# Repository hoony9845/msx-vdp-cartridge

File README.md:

# MSX V9990 / V9968 Emulator Cartridge (RP2350)

[English](#english)

MSX 실기기에서 **V9990(GFX9000)과 V9968을 가장 저렴하게 경험**해 보기 위한 프로젝트다.
실제 V9990 칩이나 FPGA 없이 RP2350 보드 하나가 MSX 버스를 받아 VDP처럼 동작하고,
화면은 HDMI(DVI 640×480@60)로 출력한다. V9990 모드에서는 I/O 포트 0x60–0x6F를 쓴다.

| MSX 실기 동작 | Geo3D 테스트 (V9968 + geo3d) |
|---|---|
|  |  |
| **Geo3D - 최적화 중** | **V9968 - 최적화 중** |
|  |  |

> **주의: 에뮬레이터다.** 실제 칩이 아니라 소프트웨어로 VDP 동작을 흉내 낸다.
> V9990은 Yamaha 매뉴얼과 openMSX 동작을, V9968은 HRA!의 RTL을 기준으로 맞췄지만,
> 실제 V9990 칩이나 V9968 카트리지(RTL)와 결과(화면, 타이밍, 커맨드 속도 등)가 다를 수 있다.
> 알려진 차이는 아래 [알려진 위험](#알려진-위험)에 정리했다.

> **면책: 사용에 따른 모든 위험은 이용자에게 있다.** 이 프로젝트의 회로도, PCB, 펌웨어,
> 소스 코드는 "있는 그대로(AS IS)" 제공되며 어떤 보증도 하지 않는다. 이를 제작하거나 사용하면서
> 생기는 MSX 본체·주변기기·모니터의 고장, 데이터 손실 등 모든 손해와 위험은 전적으로 이용자가
> 부담하며, 제작자는 어떠한 책임도 지지 않는다.

카트리지의 슬라이드 스위치(SW1, PCB rev 0.2)로 **V9968 + geo3d v2.0**(HRA!의 V9968 카트리지 호환, 포트 88h–8Fh)도 고를 수 있다.
스위치가 포트 디코더와 펌웨어 선택을 함께 바꾼다. 스위치 없는 rev 0.1 기판은 펌웨어 설정(`-DMSX_VDP_SWITCH=OFF`, USB 시리얼 `chip v9968`)으로 고른다.
자세한 내용은 [docs/v9968.md](docs/v9968.md)

- 프로토타입 보드: **Pimoroni Pico Plus 2** (RP2350B, 플래시 16MB, PSRAM 8MB)
  또는 **Waveshare Core2350B1/B2** (`-DPICO_BOARD=waveshare_core2350b`)
- 결선: [docs/hardware.md](docs/hardware.md)
- 카트리지 PCB (KiCad 8, JLCPCB 주문용 거버 포함): [hardware/](hardware/README.md)

> **실기 검증된 조합은 하나뿐이다:** Core2350B판 PCB(rev 0.3) + **Waveshare Core2350B2**(PSRAM 8MB).
> Pico Plus 2판 PCB와 Core2350B1(PSRAM 2MB)은 제작·검증하지 않았다.

## 구조

```
core/        이식 가능한 VDP 코어 (Pico SDK 의존성 없음, PC와 펌웨어가 공유)
  v9990.c        포트, 레지스터, 팔레트, 모드 해석, 타이밍 이벤트
  v9990_cmd.c    커맨드 엔진(블리터)
  v9990_render.c 스캔라인 렌더러 → RGB565
  v9990_vram.h   VRAM 물리 배치 (P1/P2/Bx 뱅크 인터리브)
  v9968*.c       V9968: 포트/레지스터, 커맨드 엔진(LRMM/LFMx 포함), 렌더러(스프라이트 모드 3)
  geo3d.c        geo3d v2.0 (참조 모델을 C로 옮김, V9968 커맨드 엔진에 명령 발행)
host/        PC용 테스트, 렌더 데모, 트레이스 재생기 (gcc)
tools/compare/  openMSX(GFX9000)와 도트 단위 비교 환경, 게임 기록 도구
firmware/    RP2350 펌웨어 (pico-sdk)
  src/bus.pio    버스 모니터 + 읽기 응답 PIO 프로그램
  src/bus.c      core1: 버스 이벤트 처리, 커맨드 엔진 실행, /INT
  src/dvi_out.c  HSTX DVI 출력, V9990 타이밍(VBlank, 라인 인터럽트)
  src/psram.c    PSRAM(VRAM) 초기화
  src/main.c     클럭(384MHz, HSTX 126MHz), 칩 선택, core0 렌더 루프
  src/vdp_select.c  칩 선택 설정 (플래시 저장, USB 시리얼 명령)
hardware/    카트리지 PCB (KiCad 프로젝트 생성 스크립트, 거버/BOM/CPL)
docs/        하드웨어 문서
```

## 동작 방식

```
MSX OUT ─► PIO monitor ─► DMA ─► 링버퍼 ─► core1 ─► v9990_write_port()
MSX IN  ─► PIO read SM ─► DMA ─► read_table[port] ─► PIO가 D0-D7 구동
                                      ▲
                     core1이 v9990_peek_port()로 항상 최신 값 유지
core0: DVI DMA IRQ ─► 렌더러가 2–3라인 앞서 v9990_render_line()
```

- 읽기는 CPU를 거치지 않고 PIO와 DMA만으로 응답하므로 Z80 I/O 사이클(약 700ns) 안에 충분히 들어온다.
- VRAM 512KB는 PSRAM에 둔다(내부 SRAM은 520KB라 부족).

## 빌드

툴체인 경로(이 머신 기준):

```sh
export PICO_SDK_PATH=~/tools/pico/pico-sdk
export PICO_TOOLCHAIN_PATH=~/tools/pico/toolchain
export PATH=~/tools/pico/cmake/bin:$PATH     # picotool 빌드에 cmake 3.17 이상 필요
```

### PC 테스트

```sh
cmake -S host -B build-host -G Ninja && ninja -C build-host
./build-host/test_v9990                           # 단위 테스트
./build-host/render_demo build-host/demo.ppm      # 640x480 출력 이미지 생성
```

### 펌웨어

```sh
cmake -S firmware -B build-fw -G Ninja && ninja -C build-fw
# BOOTSEL 상태로 연결한 뒤 build-fw/msx_v9990.uf2 복사
```

다른 RP2350B 보드:
`cmake -S firmware -B build-fw -DPICO_BOARD=<board> -DV9990_PSRAM_CS_PIN=<gpio>`

USB 시리얼 명령(진단용):

| 명령 | 내용 |
|---|---|
| `stat [reset]` | core1 루프·버스 이벤트·포트별 횟수, `/INT`·`/WAIT`, V9990 레지스터, 렌더 시간, DVI 상태(클럭 실측, 늦은 IRQ, 출력 재시작). `reset`은 최대값을 지운다 |
| `psram [sweep]` | PSRAM 쓰기/읽기 검사와 스트리밍 읽기 속도. `sweep`은 클럭 분주·RX 지연별로 검사한다 (VRAM을 지움) |
| `vram` | VRAM 64KB 블록별 CRC32 (PC 재생 결과와 비교용) |
| `out <포트> <값>` | V9990 포트에 직접 쓰기 (16진, MSX 없이 모드 시험) |
| `bench` | V9990: 현재 화면 한 줄의 렌더 시간(전체, 스프라이트 없이, VRAM 전부 SRAM일 때, 화면 꺼짐, VRAM 읽기 속도). V9968: 현재 화면 전체 줄의 평균·최대와 단계별 시간 |
| `dump` | V9968 상태(레지스터, 팔레트, VRAM)를 출력한다. 로그를 `host/v9968_dump_replay`로 PC에서 그려 볼 수 있다 (약 70초, 그동안 커맨드 엔진이 멈춤) |

`-DMSX_BOOT_TRACE=ON`으로 빌드하면 부팅 시 USB 터미널을 최대 60초 기다린 뒤 부팅 단계를 출력한다.
`stat`의 출력은 렌더 루프에서 나가므로, 주기적으로 보내면 그 프레임의 화면이 깨진다.

## 진행 상황

| 영역 | 상태 |
|---|---|
| 포트 P#0–P#7, 레지스터 쓰기 마스크, VRAM 포인터(R#2/R#5에서 갱신), 팔레트 | ✅ (PC 테스트) |
| 표시 모드 판정 (P1, P2, B1–B7, MCS 포함, 매뉴얼 8.3 표) | ✅ (PC 테스트) |
| 인터럽트 (VI, HI, CE), 상태 레지스터 | ✅ 기본 |
| P1 모드: 2레이어, 레이어별 팔레트, 앞/뒤 영역(R#27), 스크롤 | ✅ (PC 테스트) |
| P2 모드: 1024×512 이미지, 짝수/홀수 바이트 팔레트 | ✅ (PC 테스트) |
| P1/P2 스프라이트: 125개, 줄당 16개, 앞/뒤 우선순위, 팔레트 | ✅ (PC 테스트) |
| 세로 스크롤 분할(라인 중간 SCAY 쓰기), R512/R256 롤 | ✅ (PC 테스트) |
| 비트맵 렌더링 BP2/BP4/BP6/BD8/BD16 | ✅ (PC 테스트) |
| 커맨드: STOP, LMMC, LMMV, LMMM, CMMC, CMMM, LINE, PSET (비트맵 좌표계, FC/BC/WM 비트 위치 대응) | ✅ (PC 테스트) |
| 비트맵 커서 2개 (32×32, 팔레트/EOR, 커서 0 우선) | ✅ (PC 테스트, openMSX 동작 기준) |
| 펌웨어: PIO 버스, DVI 출력, PSRAM, 듀얼 코어 | ✅ 실기 확인 (Core2350B: Chase H.Q. 주행, Petscii Robots 게임 화면) |
| YJK/YUV, R#16 화면 위치 조정 | ⬜ TODO |
| 커맨드 P1/P2 좌표계 (openMSX와 같은 매핑, 실기 Ghosts'n Goblins에서 확인) | ✅ |
| 커맨드: LMCM, CMMK, BMxx, SRCH, POINT, ADVN | ⬜ TODO |
| HR 비트 (펌웨어: DVI 두 줄마다 토글) | ✅ 기본 |
| 커맨드 실행 시간, 라인 타이밍 정밀도, PAL 50Hz 타이밍 | ⬜ TODO |
| 15kHz RGB 출력 (PIO + 저항 DAC) | ⬜ 선택 사항 |
| **V9968 + geo3d v2.0** (펌웨어 설정으로 선택): 전 화면 모드, 스프라이트 모드 1–3, 전 커맨드, 인터럽트 | ✅ (PC 테스트, RTL·참조 모델·openMSX 포크와 비교) — [docs/v9968.md](docs/v9968.md) |

기준 자료: Yamaha V9990 Application Manual(1992), 매뉴얼에 없는 동작은 openMSX의 구현을 참고했다.
`tools/compare/`로 openMSX 16.0과 비교한 결과, 테스트 장면 전부가 도트 단위로 일치한다.
실제 게임에서는 다음과 같다.
- **Chase H.Q. V9990**(DiHalt Studio, 90초 플레이): 캡처 78장 중 76장이 일치한다. 나머지 2장도 그 시점의 VRAM은 openMSX와 같다(화면 스캔 타이밍 차이).
- **Another World**(Edd Biddulph, 터보 R, 4분 인트로): 113장 모두 일치한다.
- MSXdev/Mapax 작품(openMSX 60초 자동 입력, 전원 직후 화면 제외):
  - **Attack of the Petscii Robots**(P1, 스프라이트): 33장 모두 일치.
  - **MSX in a Row**(B3 BD16, LMMC, 비트맵 커서): 21장 일치, 11장은 0.1% 미만(커서 아래 끝 1줄, 미확인).
  - **Dreams Puzzle**(B3 BD16, LINE), **Mr. Balloon remake**(B7 1024 BP4): VRAM이 26/30 시점에서 같고,
    나머지는 직전 프레임에 시작된 커맨드 영역뿐이다(openMSX는 커맨드에 시간이 걸림). B7 화면은 openMSX
    캡처가 640픽셀로 줄어 도트 비교를 할 수 없다.
- **Ghosts'n Goblins**(ASM Team, V9990 데모, Konami SCC 2MB, B1 BP6/BP4 + P1 스프라이트, P1에서 LMMV/LMMM):
  직접 플레이한 기록 66장 모두 일치. P1 커맨드 좌표계가 없을 때는 악마 스프라이트가 깨졌다.
펌웨어의 렌더러는 스캔보다 2–3줄 앞서 그리므로, 화면 중간의 레지스터 변경은 몇 줄 일찍 적용된다(TODO).
새 프레임은 첫 줄 4줄 전에 시작한다(라인 카운터 리셋): 그 전에 VI 핸들러가 쓴 스크롤이 첫 줄부터 적용된다.

코드의 `VERIFY` 주석은 V9990 Application Manual이나 openMSX와 아직 대조하지 않은 부분이다
(표시 모드 표, 비트 순서, NX/NY=0의 의미 등).

## 다음 단계

1. 다른 GFX9000 소프트웨어(P1/P2, 스프라이트, 커맨드 엔진)로 실기 호환성 테스트
2. PAL(R#7 bit 3) 게임: VI를 50Hz로 낼지 결정 (HDMI 출력은 60Hz 고정)
3. 커맨드 엔진 속도: 게임 진행 중 PSRAM 경합으로 렌더 시간이 늘어난다 (B1 평균 34us/63us)

## 알려진 위험

- **읽기마다 `/WAIT`**: 읽기 SM이 모든 읽기에서 `/WAIT`를 걸고, core1이 앞선 접근을 모두 처리한 뒤에 응답한다
  (쓰기 직후의 상태 읽기, 같은 포트 연속 읽기도 순서대로 맞는다). 그만큼 읽기 사이클이 길어진다. core1이 20us 안에
  응답하지 못하면 `stat`의 ordered-read timeouts가 늘어난다.
- **렌더 시간**: VRAM0(물리 0x00000-0x3FFFF)은 SRAM, VRAM1은 PSRAM이다. 비트맵 한 줄은 XIP 스트리밍 DMA로
  읽는다(126MHz). 한계에 가까운 모드: B3 512×424 BD8 줄당 약 29us(한계 31.7us), P1(Petscii Robots)
  평균 60us(한계 63us). BD16 512×424는 아직 측정하지 않았다.
- **P1/P2 이름 표 캐시**: 이름 표 한 줄은 타일 행(8줄)마다 한 번 읽는다. 프레임 중간에 바뀐 이름은 그 타일 행의
  나머지 줄에서 다음 프레임에 보일 수 있다.
- **PSRAM 126MHz**: Core2350B 한 장에서 RX 지연 2–5가 정상(3 사용). 온도 여유는 미확인.
- **384MHz 오버클럭 + 1.30V**: clk_sys는 pll_usb(384MHz), HSTX는 pll_sys(252MHz)/2. HSTX 분주기는 정수
  분주만 되고 듀티 보정이 없어서, clk_sys/3(378MHz)에서는 모니터 화면이 대부분 검게 나왔다. Core2350B 한 장에서
  확인했고 개체별·온도별 여유는 미확인.
- **V9968 2줄 앞서 렌더**: 스프라이트 모드 3이 많은 화면(LUMEN FORGE)은 줄당 최대 약 90us라 바로 앞 줄에서
  그리면(31.7us) 늦는다. 대신 줄 인터럽트로 바꾼 레지스터가 실제 카트리지보다 2줄 늦게 보인다.
- **V9968 LRMM 속도**: core1의 LRMM이 실제 칩(픽셀당 약 12클럭)보다 수 배 느려서, LRMM으로 화면 전체를
  그리는 데모(SUPER CAT 약 11fps)는 실제보다 느리게 움직인다. 결과는 HRA의 vdp_command.v와 같다.

## 참고

- Yamaha V9990 E-VDP-III Application Manual
- openMSX `src/video/v9990/` (동작만 참고, 코드는 가져오지 않음)
- pico-examples `hstx/dvi_out_hstx_encoder`

## 라이선스

- 소프트웨어(`core/`, `firmware/`, `host/`, `tools/`): MIT (`LICENSE`)
- 하드웨어(`hardware/`): CERN-OHL-P v2 (`hardware/LICENSE`)
- 예외: V9968 코어(`core/v9968*.c`, `core/v9968.h`)는 HRA!의 V9968 RTL을 따라 만들었기 때문에
  그 RTL의 조건을 따른다(저작권 표시 유지, 허락 없는 판매·상업적 사용 금지).
  이 코어가 들어간 펌웨어 바이너리(`.uf2`)를 배포할 때도 같은 표시를 함께 넣어야 한다.
- 외부 코드와 참고 자료의 표시: `THIRD_PARTY_NOTICES.md`
- 모든 라이선스는 보증 없이(AS IS) 제공되며, 사용에 따른 위험과 책임은 이용자에게 있다(위의 면책 참고).

---

# English

This project is the **cheapest way to try the V9990 (GFX9000) and the V9968 on a real MSX**.
There is no real V9990 chip or FPGA: a single RP2350 board listens to the MSX bus and behaves like the VDP,
and the picture goes out over HDMI (DVI 640×480@60). In V9990 mode it uses I/O ports 0x60–0x6F.

| On a real MSX | Geo3D test (V9968 + geo3d) |
|---|---|
|  |  |
| **Geo3D - optimisation in progress** | **V9968 - optimisation in progress** |
|  |  |

> **Note: this is an emulator.** The VDP is imitated in software, not built as a chip.
> The V9990 follows the Yamaha manual and openMSX's behaviour, the V9968 follows HRA!'s RTL,
> but results (picture, timing, command speed, ...) can differ from a real V9990 chip or the V9968
> cartridge (RTL). Known differences are listed under [Known risks](#known-risks).

> **Disclaimer: you use this project entirely at your own risk.** The schematics, PCB, firmware and
> source code are provided "AS IS", without any warranty. All damage and risk from building or using
> them, including failure of the MSX, peripherals or monitor and loss of data, are borne entirely by
> the user; the author accepts no liability whatsoever.

The cartridge's slide switch (SW1, PCB rev 0.2) also selects **V9968 + geo3d v2.0** (compatible with HRA!'s
V9968 cartridge, ports 88h–8Fh). The switch changes both the port decoder and the firmware's choice.
On the rev 0.1 board without the switch, choose in the firmware (`-DMSX_VDP_SWITCH=OFF`, USB serial `chip v9968`).
Details: [docs/v9968.md](docs/v9968.md) (Korean)

- Prototype boards: **Pimoroni Pico Plus 2** (RP2350B, 16MB flash, 8MB PSRAM)
  or **Waveshare Core2350B1/B2** (`-DPICO_BOARD=waveshare_core2350b`)
- Wiring: [docs/hardware.md](docs/hardware.md) (Korean)
- Cartridge PCB (KiCad 8, with Gerbers for JLCPCB): [hardware/](hardware/README.md) (Korean)

> **Only one combination has been verified on hardware:** the Core2350B PCB (rev 0.3) + **Waveshare Core2350B2** (8MB PSRAM).
> The Pico Plus 2 PCB and the Core2350B1 (2MB PSRAM) have not been built or tested.

## Layout

```
core/        portable VDP core (no Pico SDK dependencies, shared by the PC and the firmware)
  v9990.c        ports, registers, palette, mode decoding, timing events
  v9990_cmd.c    command engine (blitter)
  v9990_render.c scanline renderer -> RGB565
  v9990_vram.h   physical VRAM layout (P1/P2/Bx bank interleave)
  v9968*.c       V9968: ports/registers, command engine (incl. LRMM/LFMx), renderer (sprite mode 3)
  geo3d.c        geo3d v2.0 (reference model ported to C, issues commands to the V9968 engine)
host/        PC tests, render demo, trace replayers (gcc)
tools/compare/  dot-exact comparison against openMSX (GFX9000), game recording tools
firmware/    RP2350 firmware (pico-sdk)
  src/bus.pio    bus monitor + read response PIO programs
  src/bus.c      core1: bus events, command engine, /INT
  src/dvi_out.c  HSTX DVI output, V9990 timing (VBlank, line interrupts)
  src/psram.c    PSRAM (VRAM) setup
  src/main.c     clocks (384MHz, HSTX 126MHz), chip selection, core0 render loop
  src/vdp_select.c  chip selection setting (stored in flash, USB serial command)
hardware/    cartridge PCB (KiCad project generator scripts, Gerbers/BOM/CPL)
docs/        hardware documents
```

## How it works

```
MSX OUT ─► PIO monitor ─► DMA ─► ring buffer ─► core1 ─► v9990_write_port()
MSX IN  ─► PIO read SM ─► DMA ─► read_table[port] ─► PIO drives D0-D7
                                      ▲
                     core1 keeps it current with v9990_peek_port()
core0: DVI DMA IRQ ─► renderer runs v9990_render_line() 2–3 lines ahead
```

- Reads are answered by PIO and DMA alone, without the CPU, well inside a Z80 I/O cycle (about 700ns).
- The 512KB of VRAM lives in PSRAM (the 520KB of internal SRAM is not enough).

## Build

Toolchain paths (on the development machine):

```sh
export PICO_SDK_PATH=~/tools/pico/pico-sdk
export PICO_TOOLCHAIN_PATH=~/tools/pico/toolchain
export PATH=~/tools/pico/cmake/bin:$PATH     # picotool needs cmake 3.17 or later
```

### PC tests

```sh
cmake -S host -B build-host -G Ninja && ninja -C build-host
./build-host/test_v9990                           # unit tests
./build-host/render_demo build-host/demo.ppm      # 640x480 output image
```

### Firmware

```sh
cmake -S firmware -B build-fw -G Ninja && ninja -C build-fw
# connect in BOOTSEL mode and copy build-fw/msx_v9990.uf2
```

Other RP2350B boards:
`cmake -S firmware -B build-fw -DPICO_BOARD=<board> -DV9990_PSRAM_CS_PIN=<gpio>`

USB serial commands (diagnostics):

| Command | What it does |
|---|---|
| `stat [reset]` | core1 loop, bus events, counts per port, `/INT` and `/WAIT`, V9990 registers, render times, DVI state (measured clocks, late IRQs, output restarts). `reset` clears the maxima |
| `psram [sweep]` | PSRAM write/read check and streaming read speed. `sweep` checks every clock divider and RX delay (clears VRAM) |
| `vram` | CRC32 of each 64KB VRAM block (to compare with a PC replay) |
| `out <port> <value>` | write a V9990 port directly (hex; tries modes without an MSX) |
| `bench` | V9990: render time of one line of the current picture (full, without sprites, with all VRAM in SRAM, display off, VRAM read speed). V9968: average and maximum over all lines of the current picture, per stage |
| `dump` | prints the V9968 state (registers, palette, VRAM); `host/v9968_dump_replay` draws the log on the PC (about 70 s, the command engine stops meanwhile) |

Built with `-DMSX_BOOT_TRACE=ON`, the firmware waits up to 60 s for a USB terminal at boot and prints the boot steps.
`stat` prints from the render loop, so sending it periodically breaks the picture of that frame.

## Status

| Area | Status |
|---|---|
| Ports P#0–P#7, register write masks, VRAM pointers (updated on R#2/R#5), palette | ✅ (PC tests) |
| Display mode decoding (P1, P2, B1–B7, incl. MCS, manual table 8.3) | ✅ (PC tests) |
| Interrupts (VI, HI, CE), status registers | ✅ basic |
| P1: two layers, palette per layer, front/back areas (R#27), scrolling | ✅ (PC tests) |
| P2: 1024×512 image, even/odd byte palettes | ✅ (PC tests) |
| P1/P2 sprites: 125, 16 per line, front/back priority, palettes | ✅ (PC tests) |
| Vertical scroll splits (SCAY written mid-line), R512/R256 roll | ✅ (PC tests) |
| Bitmap rendering BP2/BP4/BP6/BD8/BD16 | ✅ (PC tests) |
| Commands: STOP, LMMC, LMMV, LMMM, CMMC, CMMM, LINE, PSET (bitmap coordinates, FC/BC/WM bit positions) | ✅ (PC tests) |
| Two bitmap cursors (32×32, palette/EOR, cursor 0 first) | ✅ (PC tests, after openMSX's behaviour) |
| Firmware: PIO bus, DVI output, PSRAM, dual core | ✅ on hardware (Core2350B: Chase H.Q. racing, Petscii Robots in game) |
| YJK/YUV, R#16 display adjust | ⬜ TODO |
| Command P1/P2 coordinate systems (same mapping as openMSX, checked with Ghosts'n Goblins on hardware) | ✅ |
| Commands: LMCM, CMMK, BMxx, SRCH, POINT, ADVN | ⬜ TODO |
| HR bit (firmware: toggles every two DVI lines) | ✅ basic |
| Command timing, line timing accuracy, PAL 50Hz timing | ⬜ TODO |
| 15kHz RGB output (PIO + resistor DAC) | ⬜ optional |
| **V9968 + geo3d v2.0** (chosen by the firmware setting): all screen modes, sprite modes 1–3, all commands, interrupts | ✅ (PC tests, compared with the RTL, the reference model and the openMSX fork) — [docs/v9968.md](docs/v9968.md) |

References: Yamaha V9990 Application Manual (1992); where the manual is silent, openMSX's implementation.
Compared with openMSX 16.0 through `tools/compare/`, every test scene matches dot for dot.
In real games:
- **Chase H.Q. V9990** (DiHalt Studio, 90 s of play): 76 of 78 captures match. For the other 2 the VRAM at that moment equals openMSX's (a difference in scan timing).
- **Another World** (Edd Biddulph, turbo R, 4-minute intro): all 113 match.
- MSXdev/Mapax titles (60 s of automatic input in openMSX, power-on screens excluded):
  - **Attack of the Petscii Robots** (P1, sprites): all 33 match.
  - **MSX in a Row** (B3 BD16, LMMC, bitmap cursor): 21 match, 11 differ by under 0.1% (one line at the bottom of the cursor, not investigated).
  - **Dreams Puzzle** (B3 BD16, LINE), **Mr. Balloon remake** (B7 1024 BP4): VRAM equal at 26 of 30 points;
    the rest is only the area of a command started in the previous frame (openMSX gives commands time).
    The B7 picture cannot be compared dot by dot because openMSX scales its capture to 640 pixels.
- **Ghosts'n Goblins** (ASM Team, V9990 demo, Konami SCC 2MB, B1 BP6/BP4 + P1 sprites, LMMV/LMMM in P1):
  all 66 shots of a recorded play match. Without the P1 command coordinates the demon sprite was garbled.

The firmware renderer draws 2–3 lines ahead of the scan, so register changes mid-picture take effect a few lines early (TODO).
A new frame starts 4 lines before its first line (line counter reset), so scroll values written by the VI handler apply from the first line.

`VERIFY` comments in the code mark what has not yet been checked against the V9990 Application Manual or openMSX
(the display mode table, bit orders, the meaning of NX/NY = 0, ...).

## Next steps

1. Compatibility tests on hardware with other GFX9000 software (P1/P2, sprites, command engine)
2. PAL games (R#7 bit 3): decide whether VI runs at 50Hz (the HDMI output is fixed at 60Hz)
3. Command engine speed: PSRAM contention during play lengthens render times (B1 average 34us of 63us)

## Known risks

- **`/WAIT` on every read**: the read SM asserts `/WAIT` on every read and answers after core1 has applied every
  earlier access (a status read right after a write, or back-to-back reads of one port, come out in order). Read
  cycles get longer by that much. If core1 does not answer within 20us, `stat` counts an ordered-read timeout.
- **Render time**: VRAM0 (physical 0x00000-0x3FFFF) is in SRAM, VRAM1 in PSRAM. A bitmap line is read with XIP
  streaming DMA (126MHz). Modes near the limit: B3 512×424 BD8 about 29us a line (limit 31.7us), P1 (Petscii Robots)
  60us average (limit 63us). BD16 512×424 not measured yet.
- **P1/P2 name table cache**: a name table row is read once per tile row (8 lines). A name changed mid-frame may
  show on the remaining lines of that tile row only in the next frame.
- **PSRAM at 126MHz**: RX delays 2–5 work on one Core2350B (3 is used). Temperature margin unknown.
- **384MHz overclock at 1.30V**: clk_sys from pll_usb (384MHz), HSTX from pll_sys (252MHz)/2. The HSTX divider
  only divides by integers and has no duty-cycle correction, so at clk_sys/3 (378MHz) the monitor showed mostly black.
  Checked on one Core2350B; margins across boards and temperatures unknown.
- **V9968 renders two lines ahead**: pictures with much sprite mode 3 (LUMEN FORGE) take up to about 90us a line,
  too late when drawn just before the line (31.7us). In exchange, registers changed by line interrupts show two lines
  later than on the real cartridge.
- **V9968 LRMM speed**: LRMM on core1 is several times slower than the real chip (about 12 clocks per pixel), so demos
  that draw the whole picture with LRMM (SUPER CAT about 11 fps) move slower than on the real thing. The results
  equal HRA's vdp_command.v.

## References

- Yamaha V9990 E-VDP-III Application Manual
- openMSX `src/video/v9990/` (behaviour only, no code taken)
- pico-examples `hstx/dvi_out_hstx_encoder`

## License

- Software (`core/`, `firmware/`, `host/`, `tools/`): MIT (`LICENSE`)
- Hardware (`hardware/`): CERN-OHL-P v2 (`hardware/LICENSE`)
- Exception: the V9968 core (`core/v9968*.c`, `core/v9968.h`) follows HRA!'s V9968 RTL and therefore keeps
  that RTL's conditions (keep the copyright notice; no sale or commercial use without permission).
  Firmware binaries (`.uf2`) containing this core must carry the same notice when distributed.
- Notices for third-party code and references: `THIRD_PARTY_NOTICES.md`
- All licences come without warranty (AS IS); the risk and responsibility of use lie with the user (see the disclaimer above).

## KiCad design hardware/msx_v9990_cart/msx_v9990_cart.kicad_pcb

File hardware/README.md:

# MSX V9990 카트리지 PCB (KiCad 8)

RP2350 모듈을 얹는 MSX 카트리지 기판. 회로 설명은 [../docs/hardware.md](../docs/hardware.md) 참고.
같은 생성 스크립트로 두 가지 버전을 만든다(외형, 엣지 커넥터, 구멍 H1/H2, 버스 회로는 동일).

| 버전 | 모듈 | KiCad 프로젝트 | 제조 파일 | 빌드 |
|---|---|---|---|---|
| Pico Plus 2 | Pimoroni Pico Plus 2 (2×20 핀헤더) | `msx_v9990_cart/` | `fab/` | `./build.sh` |
| Core2350B | Waveshare Core2350B **B1(2MB) 또는 B2(8MB) PSRAM판** (2×8 핀헤더 4개) | `msx_v9990_cart_core2350b/` | `fab_core2350b/` | `MSX_VARIANT=core2350b ./build.sh` |

> **검증 상태:** 실기에서 확인한 것은 **Core2350B판 rev 0.3 + Waveshare Core2350B2(PSRAM 8MB)** 뿐이다.
> Pico Plus 2판과 Core2350B1(PSRAM 2MB) 조합은 제작·검증하지 않았다.

### Core2350B 버전 메모

- PSRAM이 모듈 뒷면에 있으므로 **반드시 핀헤더로 띄워서** 장착한다. 모듈 아래에는 배선과 비아가 지나간다.
- USB, BOOTSEL, RESET은 모듈의 **FFC 커넥터 + Waveshare USB 어댑터**를 쓴다(카트리지에는 없음).
  FFC 커넥터는 모듈 왼쪽 위 모서리 쪽에 오며, 케이블은 모듈 위로 지나간다.
- 전원: MSX +5V → D1(쇼트키) → 모듈 VBUS. USB 어댑터 연결 시 USB 전원이 MSX 쪽으로 역류하지 않는다.
- GPIO 할당과 PSRAM CS(GP47)는 Pico Plus 2판과 같다. 펌웨어는 `cmake -DPICO_BOARD=waveshare_core2350b`로 빌드.
- 모듈 핀 배치는 Waveshare 회로도(Core2350B.pdf)의 P1–P4 헤더와 제품 사진의 실크 표기를 대조해 정했다.
  **주문 전에 구멍 확인용 PDF(`fab_core2350b/*_hole_check*.pdf`) 위에 모듈 실물을 올려 확인할 것.**
- 패드 번호: 1–16 = P1, 17–32 = P2, 33–48 = P3, 49–64 = P4.

- **rev 0.2**: VDP 선택 슬라이드 스위치 SW1(C&K JS202011AQN, DPDT 직각형)을 기판 위쪽 가장자리, HDMI 커넥터 오른쪽에 추가했다(레버가 위쪽 가장자리 밖으로 약 1.2mm 나옴).
  - SW1이 디코더 비교값(V9990: 60h–6Fh, V9968: 88h–8Fh)과 GP22를 바꾼다.
  - 보조 부품으로 R10/R11(10k)을 추가했다.
  - GP22는 /WR 대신 SW1을 읽는다. U2는 /WR을 받지만 출력은 비워 둔다.
  - SW1은 스루홀 부품이라 손으로 납땜한다. 카트리지 케이스를 쓰면 레버 자리를 파 줘야 한다.
- **rev 0.3**: 외곽선을 Overrich 카트리지 케이스(Konami형)에 맞췄다.
  - 기준은 MSXLegend의 KC MSX FLASH V3 거버(Overrich 케이스용, github.com/msxlegend/KC-MSX-FLASH)이고, 엣지 핑거 끝선에 맞춰 옮겨 왔다.
  - rev 0.2 대비 차이:
    - 위로 1.96mm, 왼쪽 0.4mm, 오른쪽 0.9mm 넓어졌다.
    - 엣지 탭이 2.07mm 길어졌다(11.89mm).
    - 왼쪽 아래 노치가 2.4mm 높아졌다.
    - 케이스 기둥 구멍 H1/H2가 Ø5.0에서 Ø4.36으로 바뀌고 약 0.7mm 위로 올라갔다.
  - 핑거 위치와 치수(1.5 × 8 mm, 2.54mm 피치)는 그대로다.
  - 엣지 탭이 길어진 만큼 버스 IC U1–U3을 2mm 위로 올렸다(핑거에서 IC로 들어가는 배선 자리).
  - HDMI 커넥터(J2)와 SW1은 위쪽 가장자리를 따라 같이 올라갔고, SW1은 오른쪽 모서리에서 8mm 안쪽(x 116.5 → 108.5)으로 옮겼다. 케이스 위쪽에 HDMI 구멍과 SW1 레버 자리는 직접 파야 한다.
  - 기판 폭이 100mm를 넘어서(101.09mm) JLCPCB 최저가(100 × 100 mm 이하) 구간에서 벗어난다.
- 2층, 1.6mm, 101.09 × 64.77 mm (엣지 탭 64.79 × 11.89 mm)
- 엣지 커넥터 치수는 실제 슬롯에 맞는 것으로 검증된 costarc의 MSX-Protoboard 카트리지를 따르고, 외곽선과 기둥 구멍은 Overrich 케이스용 KC MSX FLASH V3를 따름
- 홀수 핀은 뒷면(B.Cu), 짝수 핀은 앞면(F.Cu)에 있고, 앞면에서 볼 때 1·2번 핀이 오른쪽 끝

## 파일

```
hardware/
  build.sh                 전체 재생성: 회로도 → PCB → 자동 배선 → GND 면 → ERC/DRC → 제조 파일
  gen/design.py            ★ 넷리스트의 원본 (부품, 핀-넷 연결). 회로를 바꿀 때는 여기만 수정
  gen/gen_schematic.py     회로도(.kicad_sch)와 프로젝트 심볼 라이브러리 생성
  gen/gen_pcb.py           배치, 외곽선, 실크, 금지 영역, HDMI 팬아웃
  gen/route.py             Freerouting 자동 배선 (여러 전략을 시도해 미배선 0인 결과 사용)
  gen/finish_pcb.py        GND 팬아웃, 앞뒷면 GND 면, 스티칭 비아
  gen/export_fab.py        거버, 드릴, BOM, CPL, 회로도 PDF
  gen/export_hole_check.py 구멍 위치 확인용 1:1 인쇄 PDF (fab/*_hole_check.pdf)
  msx_v9990_cart/          KiCad 프로젝트 (KiCad에서 열어 보거나 수정 가능)
  fab/                     ★ JLCPCB 주문용 출력물
  reports/                 ERC / DRC 보고서
```

KiCad에서 직접 수정해도 되지만, `build.sh`를 다시 실행하면 덮어쓰니 주의.
생성기를 고치는 쪽을 권장한다.

```sh
cd hardware && ./build.sh      # 2~5분 (자동 배선 포함)
```

필요한 것: KiCad 8 (`kicad-cli`, pcbnew 파이썬 모듈), `~/tools/freerouting/freerouting-2.4.1.jar`, Java 25 (`~/tools/jre25`).

## 검증 결과 (현재 버전)

| 항목 | 결과 |
|---|---|
| ERC | 0 errors, 0 warnings |
| DRC (회로도 일치 검사 포함) | 0 violations, 미연결 0, 풋프린트 오류 0 |
| 넷리스트 대조 | design.py와 회로도 넷 일치 (DRC schematic parity) |

## JLCPCB 주문

업로드: `fab/msx_v9990_cart_gerbers_jlcpcb.zip`

| 항목 | 값 |
|---|---|
| Layers | 2 |
| Dimensions | 101.09 × 64.77 mm (자동 인식) |
| PCB Thickness | **1.6 mm** |
| Surface Finish | ENIG 권장 (HASL도 가능) |
| **Gold Fingers** | **Yes**, **45° finger chamfer(베벨) 선택** |
| Min via hole | 0.3 mm |
| Min track/spacing | 0.15 mm (GND 면의 가장 좁은 부분 0.14 mm, JLC 최소 0.127 mm 이내) |

SMT 조립까지 맡길 경우:
- `fab/msx_v9990_cart_bom_jlcpcb.csv`, `fab/msx_v9990_cart_cpl_jlcpcb.csv` 업로드
- BOM의 `LCSC Part #` 칸은 비워 두었다. JLC 부품 검색에서 MPN으로 찾아 채울 것
- M1(Pico Plus 2)은 손으로 핀헤더 장착, SW1(스루홀 슬라이드 스위치)도 손납땜
- J2(HDMI)는 스루홀 실드 핀이 있어 CPL에서 빠져 있다. 손납땜하거나 JLC 부품이 있으면 추가할 것
- JLC 미리보기에서 SOIC 부품의 회전 방향(1번 핀 위치)을 반드시 확인할 것

## 조립 순서

1. SMD 부품: U1–U5 (SOIC), R1–R9, C1–C7, D1 (방향: 캐소드 띠가 Pico 쪽)
2. J2 HDMI 커넥터
3. M1: **2×20 핀헤더로 장착** (소켓 또는 직접 납땜). 모듈 아래로 신호선과 비아가 지나가므로 모듈을 기판에 바로 붙이지 말 것
4. 펌웨어 기록 (USB-C, BOOTSEL) 후 MSX에 삽입. **실크의 "LABEL SIDE / PINS 2-50" 면이 카트리지 라벨 방향**

## 주문 전에 직접 확인할 것

자동 검사(ERC/DRC)로는 잡을 수 없는 항목들이다.

1. **엣지 커넥터 방향**: 이 기판은 msx.org 위키와 두 오픈소스 카트리지 설계의 공통 규칙을 따랐다(짝수 핀이 라벨면).
   가지고 있는 상용 카트리지에서 1번 핀(/CS1) 쪽이 어느 면 어느 끝인지 한 번 대조할 것.
2. **HDMI 커넥터 품번**: 풋프린트는 Amphenol 10029449-x01xLF 기준이다. 다른 제품을 사면 핀 간격과 실드 위치가 다를 수 있다.
3. **Pico Plus 2 핀배치**: Raspberry Pi Pico와 같은 40핀 배치(GND 3·8·13·18·23·28·33·38번, VSYS 39번, 3V3 36번)라고 가정했다. Pimoroni 핀아웃 문서로 확인할 것.
4. **슬롯 높이 여유**: 핀헤더로 올린 Pico 높이는 약 10mm다. 사용할 MSX의 슬롯 덮개와 간섭하지 않는지 확인할 것.
5. **/BUSDIR**: 오픈 드레인(74LVC07)으로 구동하며 본체에 풀업이 있다고 가정했다.

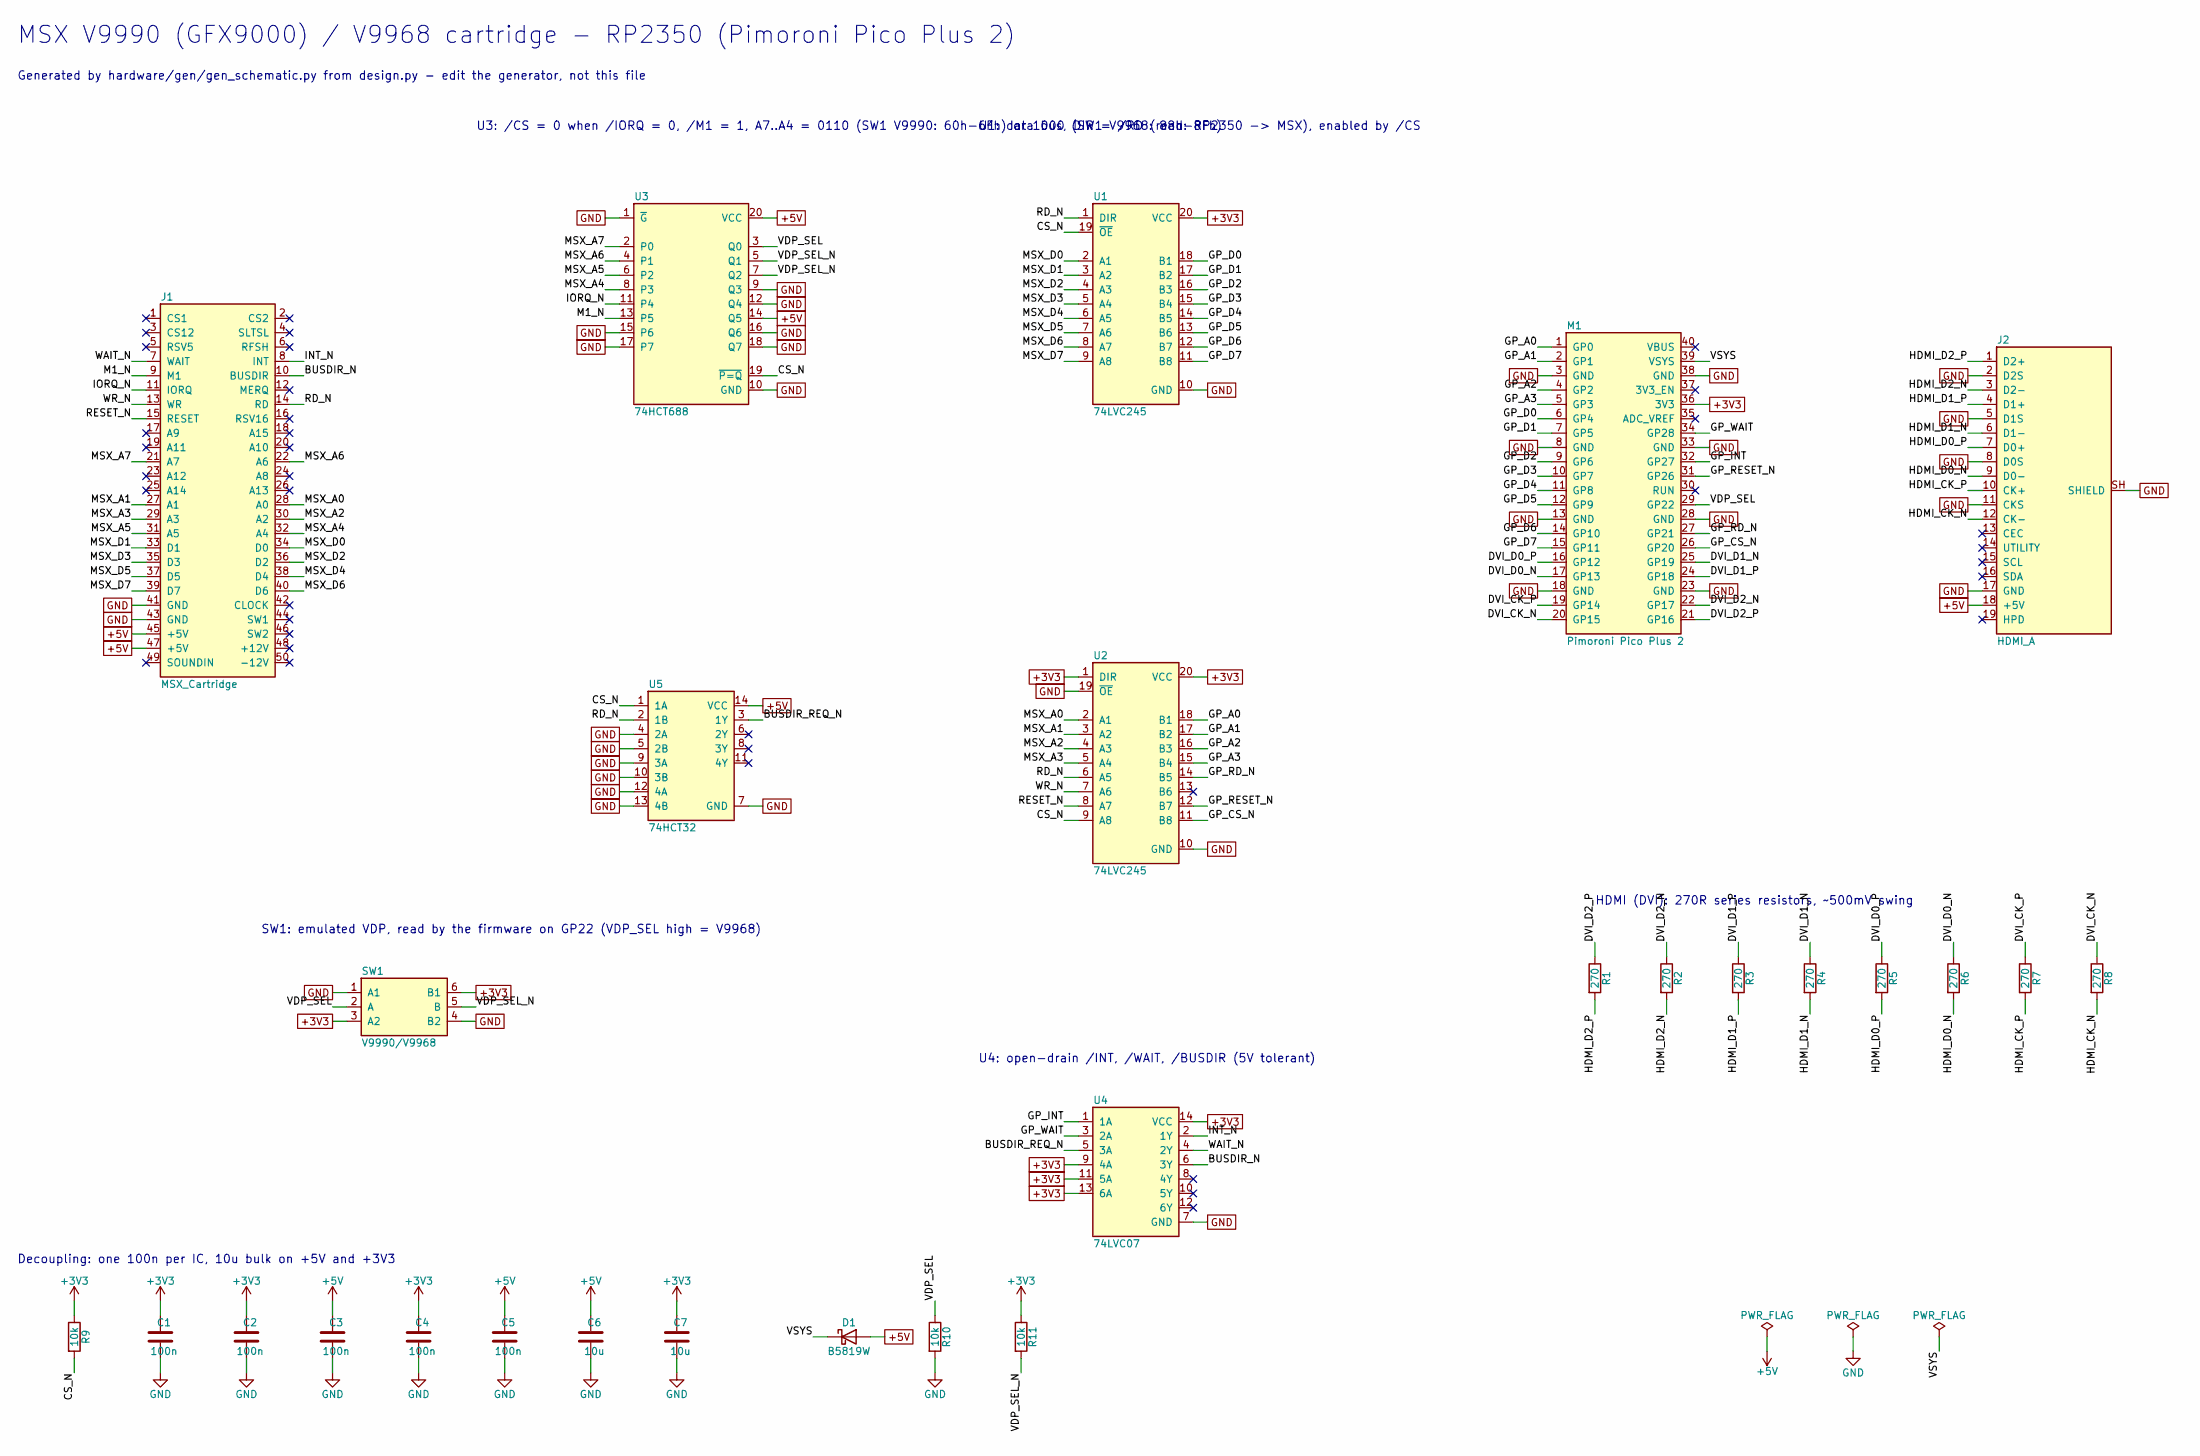
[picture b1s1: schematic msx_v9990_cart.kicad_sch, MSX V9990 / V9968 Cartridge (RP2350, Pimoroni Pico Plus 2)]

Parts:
C1, C2, C3, C4, C5: 100n; C_0805_2012Metric; MPN CL21B104KBCNNNC
C6, C7: 10u; C_0805_2012Metric; MPN CL21A106KAYNNNE
D1: B5819W; D_SOD-123; MPN B5819W
J1: MSX_Cartridge; MSX_Cartridge_Edge
J2: HDMI_A; HDMI_A_Amphenol_10029449-x01xLF_Horizontal; MPN 10029449-001RLF
M1: Pimoroni Pico Plus 2; RaspberryPi_Pico_Common_THT
R1, R2, R3, R4, R5, R6, R7, R8: 270; R_0603_1608Metric; MPN 0603WAF2700T5E
R9, R10, R11: 10k; R_0805_2012Metric; MPN 0805W8F1002T5E
SW1: V9990/V9968; SW_CK_JS202011AQN_DPDT_Angled; MPN JS202011AQN
U1, U2: 74LVC245; SOIC-20W_7.5x12.8mm_P1.27mm; MPN SN74LVC245ADWR
U3: 74HCT688; SOIC-20W_7.5x12.8mm_P1.27mm; MPN 74HCT688D
U4: 74LVC07; SOIC-14_3.9x8.7mm_P1.27mm; MPN SN74LVC07AD
U5: 74HCT32; SOIC-14_3.9x8.7mm_P1.27mm; MPN 74HCT32D

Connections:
+3V3: C1.1, C2.1, C4.1, C7.1, M1.36 (3V3), R9.1, R11.1, SW1.3 (A2), SW1.6 (B1), U1.20 (VCC), U2.1 (DIR), U2.20 (VCC), U4.9 (4A), U4.11 (5A), U4.13 (6A), U4.14 (VCC)
+5V: C3.1, C5.1, C6.1, D1.2 (A), J1.45 (+5V), J1.47 (+5V), J2.18 (+5V), U3.14 (Q5), U3.20 (VCC), U5.14 (VCC)
/BUSDIR_N: J1.10 (BUSDIR), U4.6 (3Y)
/BUSDIR_REQ_N: U4.5 (3A), U5.3 (1Y)
/CS_N: R9.2, U1.19 (~OE), U2.9 (A8), U3.19 (~P=Q), U5.1 (1A)
/DVI_CK_N: M1.20 (GP15), R8.1
/DVI_CK_P: M1.19 (GP14), R7.1
/DVI_D0_N: M1.17 (GP13), R6.1
/DVI_D0_P: M1.16 (GP12), R5.1
/DVI_D1_N: M1.25 (GP19), R4.1
/DVI_D1_P: M1.24 (GP18), R3.1
/DVI_D2_N: M1.22 (GP17), R2.1
/DVI_D2_P: M1.21 (GP16), R1.1
/GP_A0: M1.1 (GP0), U2.18 (B1)
/GP_A1: M1.2 (GP1), U2.17 (B2)
/GP_A2: M1.4 (GP2), U2.16 (B3)
/GP_A3: M1.5 (GP3), U2.15 (B4)
/GP_CS_N: M1.26 (GP20), U2.11 (B8)
/GP_D0: M1.6 (GP4), U1.18 (B1)
/GP_D1: M1.7 (GP5), U1.17 (B2)
/GP_D2: M1.9 (GP6), U1.16 (B3)
/GP_D3: M1.10 (GP7), U1.15 (B4)
/GP_D4: M1.11 (GP8), U1.14 (B5)
/GP_D5: M1.12 (GP9), U1.13 (B6)
/GP_D6: M1.14 (GP10), U1.12 (B7)
/GP_D7: M1.15 (GP11), U1.11 (B8)
/GP_INT: M1.32 (GP27), U4.1 (1A)
/GP_RD_N: M1.27 (GP21), U2.14 (B5)
/GP_RESET_N: M1.31 (GP26), U2.12 (B7)
/GP_WAIT: M1.34 (GP28), U4.3 (2A)
/HDMI_CK_N: J2.12 (CK-), R8.2
/HDMI_CK_P: J2.10 (CK+), R7.2
/HDMI_D0_N: J2.9 (D0-), R6.2
/HDMI_D0_P: J2.7 (D0+), R5.2
/HDMI_D1_N: J2.6 (D1-), R4.2
/HDMI_D1_P: J2.4 (D1+), R3.2
/HDMI_D2_N: J2.3 (D2-), R2.2
/HDMI_D2_P: J2.1 (D2+), R1.2
/INT_N: J1.8 (INT), U4.2 (1Y)
/IORQ_N: J1.11 (IORQ), U3.11 (P4)
/M1_N: J1.9 (M1), U3.13 (P5)
/MSX_A0: J1.28 (A0), U2.2 (A1)
/MSX_A1: J1.27 (A1), U2.3 (A2)
/MSX_A2: J1.30 (A2), U2.4 (A3)
/MSX_A3: J1.29 (A3), U2.5 (A4)
/MSX_A4: J1.32 (A4), U3.8 (P3)
/MSX_A5: J1.31 (A5), U3.6 (P2)
/MSX_A6: J1.22 (A6), U3.4 (P1)
/MSX_A7: J1.21 (A7), U3.2 (P0)
/MSX_D0: J1.34 (D0), U1.2 (A1)
/MSX_D1: J1.33 (D1), U1.3 (A2)
/MSX_D2: J1.36 (D2), U1.4 (A3)
/MSX_D3: J1.35 (D3), U1.5 (A4)
/MSX_D4: J1.38 (D4), U1.6 (A5)
/MSX_D5: J1.37 (D5), U1.7 (A6)
/MSX_D6: J1.40 (D6), U1.8 (A7)
/MSX_D7: J1.39 (D7), U1.9 (A8)
/RD_N: J1.14 (RD), U1.1 (DIR), U2.6 (A5), U5.2 (1B)
/RESET_N: J1.15 (RESET), U2.8 (A7)
/VDP_SEL: M1.29 (GP22), R10.1, SW1.2 (A), U3.3 (Q0)
/VDP_SEL_N: R11.2, SW1.5 (B), U3.5 (Q1), U3.7 (Q2)
/VSYS: D1.1 (K), M1.39 (VSYS)
/WAIT_N: J1.7 (WAIT), U4.4 (2Y)
/WR_N: J1.13 (WR), U2.7 (A6)
GND: C1.2, C2.2, C3.2, C4.2, C5.2, C6.2, C7.2, J1.41 (GND), J1.43 (GND), J2.2 (D2S), J2.5 (D1S), J2.8 (D0S), J2.11 (CKS), J2.17 (GND), J2.SH (SHIELD), M1.3 (GND), M1.8 (GND), M1.13 (GND), M1.18 (GND), M1.23 (GND), M1.28 (GND), M1.33 (GND), M1.38 (GND), R10.2, SW1.1 (A1), SW1.4 (B2), U1.10 (GND), U2.10 (GND), U2.19 (~OE), U3.1 (~G), U3.9 (Q3), U3.10 (GND), U3.12 (Q4), U3.15 (P6), U3.16 (Q6), U3.17 (P7), U3.18 (Q7), U4.7 (GND), U5.4 (2A), U5.5 (2B), U5.7 (GND), U5.9 (3A), U5.10 (3B), U5.12 (4A), U5.13 (4B)

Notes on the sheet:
MSX V9990 (GFX9000) / V9968 cartridge - RP2350 (Pimoroni Pico Plus 2)
Generated by hardware/gen/gen_schematic.py from design.py - edit the generator, not this file
U3: /CS = 0 when /IORQ = 0, /M1 = 1, A7..A4 = 0110 (SW1 V9990: 60h-6Fh) or 1000 (SW1 V9968: 88h-8Fh)
SW1: emulated VDP, read by the firmware on GP22 (VDP_SEL high = V9968)
U1: data bus, DIR = /RD (read: RP2350 -> MSX), enabled by /CS
U4: open-drain /INT, /WAIT, /BUSDIR (5V tolerant)
HDMI (DVI): 270R series resistors, ~500mV swing
Decoupling: one 100n per IC, 10u bulk on +5V and +3V3

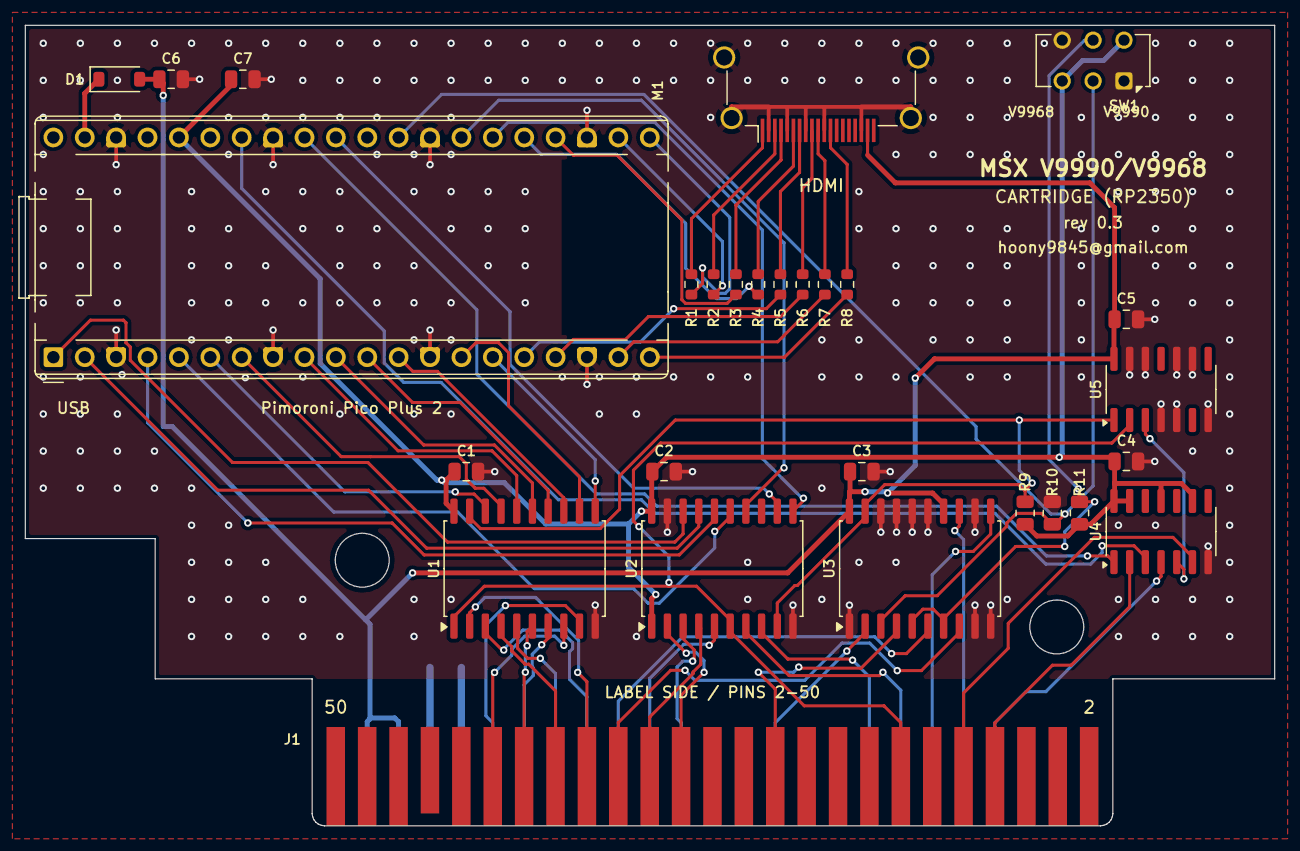
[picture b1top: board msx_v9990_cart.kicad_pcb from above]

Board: 2 copper layers, 101.1 x 64.8 mm, 28 parts (0 on the bottom side), 65 nets.

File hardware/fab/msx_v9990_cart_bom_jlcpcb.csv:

Comment,Designator,Footprint,MPN,LCSC Part #,Qty,Note
100n,"C1,C2,C3,C4,C5",C_0805_2012Metric,CL21B104KBCNNNC,,5,
10u,"C6,C7",C_0805_2012Metric,CL21A106KAYNNNE,,2,
B5819W,D1,D_SOD-123,B5819W,,1,
HDMI_A,J2,HDMI_A_Amphenol_10029449-x01xLF_Horizontal,10029449-001RLF,,1,Check that the purchased HDMI receptacle matches this footprint
Pimoroni Pico Plus 2,M1,RaspberryPi_Pico_Common_THT,,,1,Hand-mounted module on 2x20 pin headers - not assembled by JLCPCB
270,"R1,R2,R3,R4,R5,R6,R7,R8",R_0603_1608Metric,0603WAF2700T5E,,8,
10k,"R9,R10,R11",R_0805_2012Metric,0805W8F1002T5E,,3,
V9990/V9968,SW1,SW_CK_JS202011AQN_DPDT_Angled,JS202011AQN,,1,
74LVC245,"U1,U2",SOIC-20W_7.5x12.8mm_P1.27mm,SN74LVC245ADWR,,2,
74HCT688,U3,SOIC-20W_7.5x12.8mm_P1.27mm,74HCT688D,,1,
74LVC07,U4,SOIC-14_3.9x8.7mm_P1.27mm,SN74LVC07AD,,1,
74HCT32,U5,SOIC-14_3.9x8.7mm_P1.27mm,74HCT32D,,1,
